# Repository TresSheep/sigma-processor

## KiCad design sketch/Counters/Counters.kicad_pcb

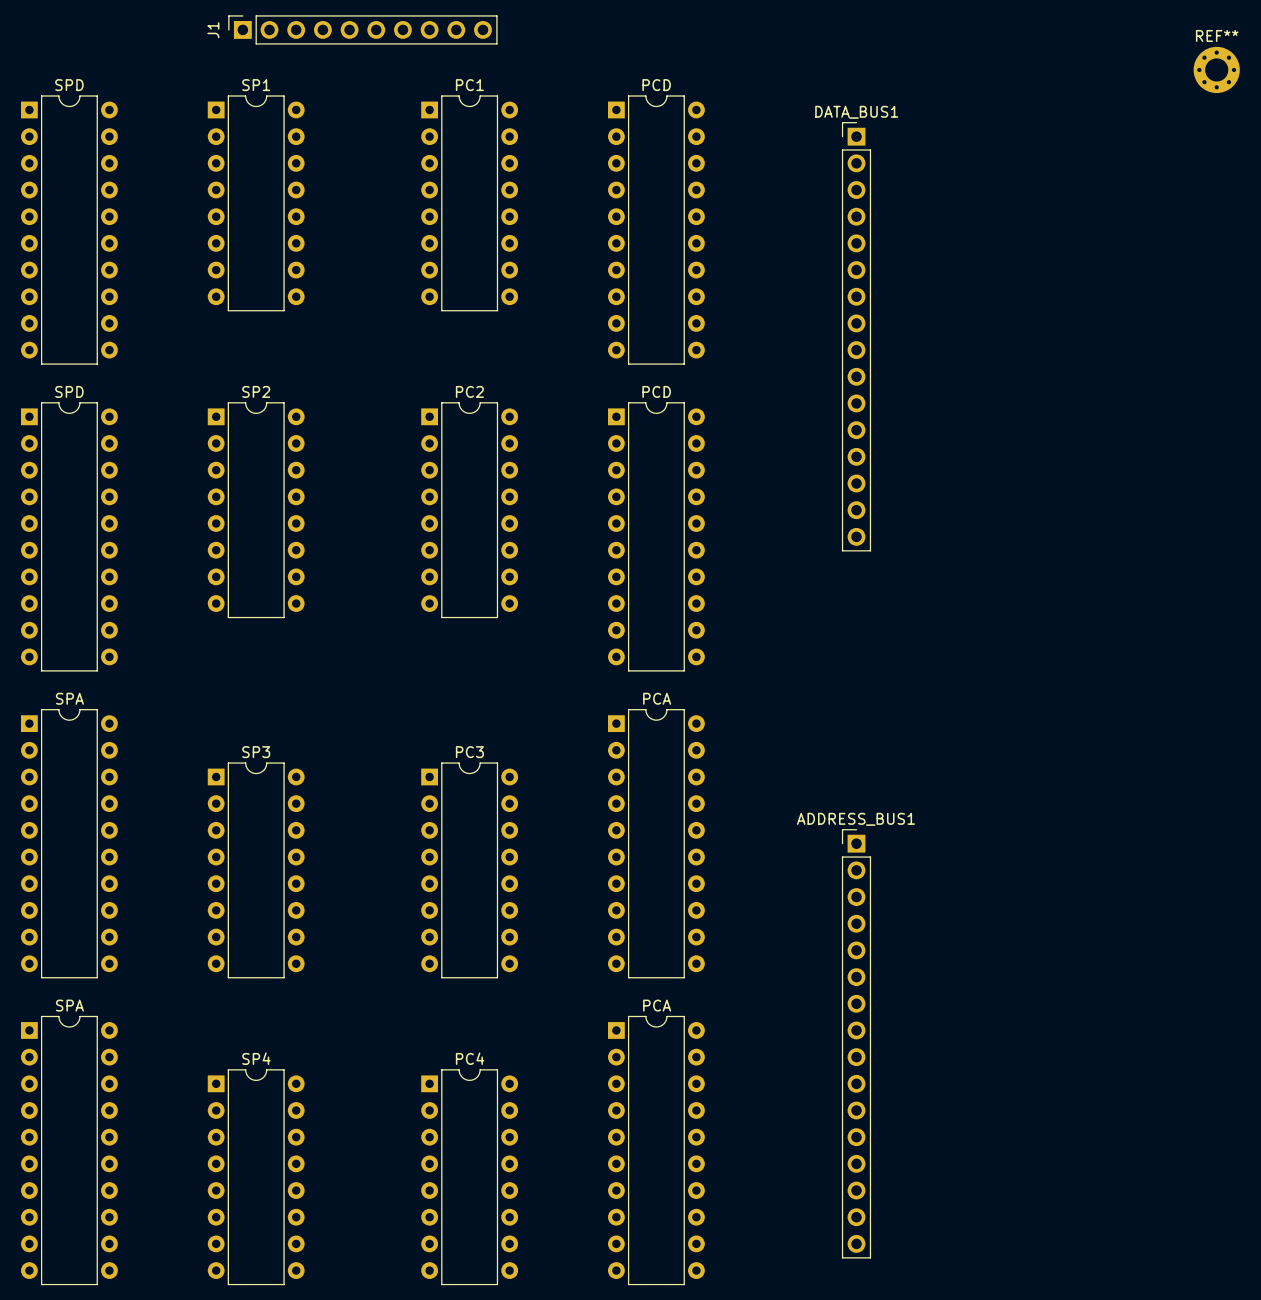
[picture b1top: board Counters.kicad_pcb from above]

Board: 2 copper layers, 19 parts (0 on the bottom side), 80 nets, no tracks yet.

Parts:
ADDRESS_BUS1: Conn_01x16; Socket_Strip_Straight_1x16_Pitch2.54mm
DATA_BUS1: Conn_01x16; Socket_Strip_Straight_1x16_Pitch2.54mm
J1: Conn_01x10; PinSocket_1x10_P2.54mm_Vertical
PC1, PC2, PC3, PC4: SN74F163AN; DIP-16_W7.62mm
PCA: SN74AHCT573N; DIP-20_W7.62mm
PCA#2: SN74AHCT573N; DIP-20_W7.62mm
PCD: SN74AHCT573N; DIP-20_W7.62mm
PCD#2: SN74AHCT573N; DIP-20_W7.62mm
SP1, SP2, SP3, SP4: SN74ALS169BN; DIP-16_W7.62mm
SPA: SN74AHCT573N; DIP-20_W7.62mm
SPA#2: SN74AHCT573N; DIP-20_W7.62mm
SPD: SN74AHCT573N; DIP-20_W7.62mm
SPD#2: SN74AHCT573N; DIP-20_W7.62mm

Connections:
+5V: J1.9, PC1.1, PC1.7, PC1.10, PC1.16, PC2.1, PC2.7, PC2.10, PC2.16, PC3.1, PC3.7, PC3.10, PC3.16, PC4.1, PC4.7, PC4.10, PC4.16, PCA.11, PCA.20, PCA#2.11, PCA#2.20, PCD.11, PCD.20, PCD#2.11, PCD#2.20, SP1.16, SP2.16, SP3.16, SP4.16, SPA.11, SPA.20, SPA#2.11, SPA#2.20, SPD.11, SPD.20, SPD#2.11, SPD#2.20
/DECSP: J1.1, SP1.2
/INCPC: J1.5, PC1.2
/LDPC: J1.6, PC1.9, PC2.9, PC3.9, PC4.9
/LDSP: J1.2, SP1.9, SP2.9, SP3.9, SP4.9
/OEPCA: J1.8, PCA.1, PCA#2.1
/OEPCD: J1.7, PCD.1, PCD#2.1
/OESPA: J1.4, SPA.1, SPA#2.1
/OESPD: J1.3, SPD.1, SPD#2.1
GND: J1.10, PC1.8, PC2.8, PC3.8, PC4.8, PCA.10, PCA#2.10, PCD.10, PCD#2.10, SP1.1, SP1.7, SP1.8, SP1.10, SP2.1, SP2.7, SP2.8, SP2.10, SP3.1, SP3.7, SP3.8, SP3.10, SP4.1, SP4.7, SP4.8, SP4.10, SPA.10, SPA#2.10, SPD.10, SPD#2.10
unnamed: ADDRESS_BUS1.1, PCA.19, SPA.19
unnamed: ADDRESS_BUS1.2, PCA.18, SPA.18
unnamed: ADDRESS_BUS1.3, PCA.17, SPA.17
unnamed: ADDRESS_BUS1.4, PCA.16, SPA.16
unnamed: ADDRESS_BUS1.5, PCA.15, SPA.15
unnamed: ADDRESS_BUS1.6, PCA.14, SPA.14
unnamed: ADDRESS_BUS1.7, PCA.13, SPA.13
unnamed: ADDRESS_BUS1.8, PCA.12, SPA.12
unnamed: ADDRESS_BUS1.9, PCA#2.19, SPA#2.19
unnamed: ADDRESS_BUS1.10, PCA#2.18, SPA#2.18
unnamed: ADDRESS_BUS1.11, PCA#2.17, SPA#2.17
unnamed: ADDRESS_BUS1.12, PCA#2.16, SPA#2.16
unnamed: ADDRESS_BUS1.13, PCA#2.15, SPA#2.15
unnamed: ADDRESS_BUS1.14, PCA#2.14, SPA#2.14
unnamed: ADDRESS_BUS1.15, PCA#2.13, SPA#2.13
unnamed: ADDRESS_BUS1.16, PCA#2.12, SPA#2.12
unnamed: DATA_BUS1.1, PC1.3, PCD.19, SP1.3, SPD.19
unnamed: DATA_BUS1.2, PC1.4, PCD.18, SP1.4, SPD.18
unnamed: DATA_BUS1.3, PC1.5, PCD.17, SP1.5, SPD.17
unnamed: DATA_BUS1.4, PC1.6, PCD.16, SP1.6, SPD.16
unnamed: DATA_BUS1.5, PC3.3, PCD.15, SP3.3, SPD.15
unnamed: DATA_BUS1.6, PC3.4, PCD.14, SP3.4, SPD.14
unnamed: DATA_BUS1.7, PC3.5, PCD.13, SP3.5, SPD.13
unnamed: DATA_BUS1.8, PC3.6, PCD.12, SP3.6, SPD.12
unnamed: DATA_BUS1.9, PC2.3, PCD#2.19, SP2.3, SPD#2.19
unnamed: DATA_BUS1.10, PC2.4, PCD#2.18, SP2.4, SPD#2.18
unnamed: DATA_BUS1.11, PC2.5, PCD#2.17, SP2.5, SPD#2.17
unnamed: DATA_BUS1.12, PC2.6, PCD#2.16, SP2.6, SPD#2.16
unnamed: DATA_BUS1.13, PC4.3, PCD#2.15, SP4.3, SPD#2.15
unnamed: DATA_BUS1.14, PC4.4, PCD#2.14, SP4.4, SPD#2.14
unnamed: DATA_BUS1.15, PC4.5, PCD#2.13, SP4.5, SPD#2.13
unnamed: DATA_BUS1.16, PC4.6, PCD#2.12, SP4.6, SPD#2.12
unnamed: SP1.11, SPA.5, SPD.5
unnamed: SP1.12, SPA.4, SPD.4
unnamed: SP1.13, SPA.3, SPD.3
unnamed: SP1.14, SPA.2, SPD.2
unnamed: SP1.15, SP3.2
unnamed: SP2.2, SP3.15
unnamed: SP2.11, SPA#2.5, SPD#2.5
unnamed: SP2.12, SPA#2.4, SPD#2.4
unnamed: SP2.13, SPA#2.3, SPD#2.3
unnamed: SP2.14, SPA#2.2, SPD#2.2
unnamed: SP2.15, SP4.2
unnamed: SP3.11, SPA.9, SPD.9
unnamed: SP3.12, SPA.8, SPD.8
unnamed: SP3.13, SPA.7, SPD.7
unnamed: SP3.14, SPA.6, SPD.6
unnamed: SP4.11, SPA#2.9, SPD#2.9
unnamed: SP4.12, SPA#2.8, SPD#2.8
unnamed: SP4.13, SPA#2.7, SPD#2.7
unnamed: SP4.14, SPA#2.6, SPD#2.6
unnamed: PC2.2, PC3.15
unnamed: PC2.11, PCA#2.5, PCD#2.5
unnamed: PC2.12, PCA#2.4, PCD#2.4
unnamed: PC2.13, PCA#2.3, PCD#2.3
unnamed: PC2.14, PCA#2.2, PCD#2.2
unnamed: PC2.15, PC4.2
unnamed: PC1.15, PC3.2
unnamed: PC3.11, PCA.9, PCD.9
unnamed: PC3.12, PCA.8, PCD.8
unnamed: PC3.13, PCA.7, PCD.7
unnamed: PC3.14, PCA.6, PCD.6
unnamed: PC4.11, PCA#2.9, PCD#2.9
unnamed: PC4.12, PCA#2.8, PCD#2.8
unnamed: PC4.13, PCA#2.7, PCD#2.7
unnamed: PC4.14, PCA#2.6, PCD#2.6
unnamed: PC1.14, PCA.2, PCD.2
unnamed: PC1.13, PCA.3, PCD.3
unnamed: PC1.12, PCA.4, PCD.4
unnamed: PC1.11, PCA.5, PCD.5

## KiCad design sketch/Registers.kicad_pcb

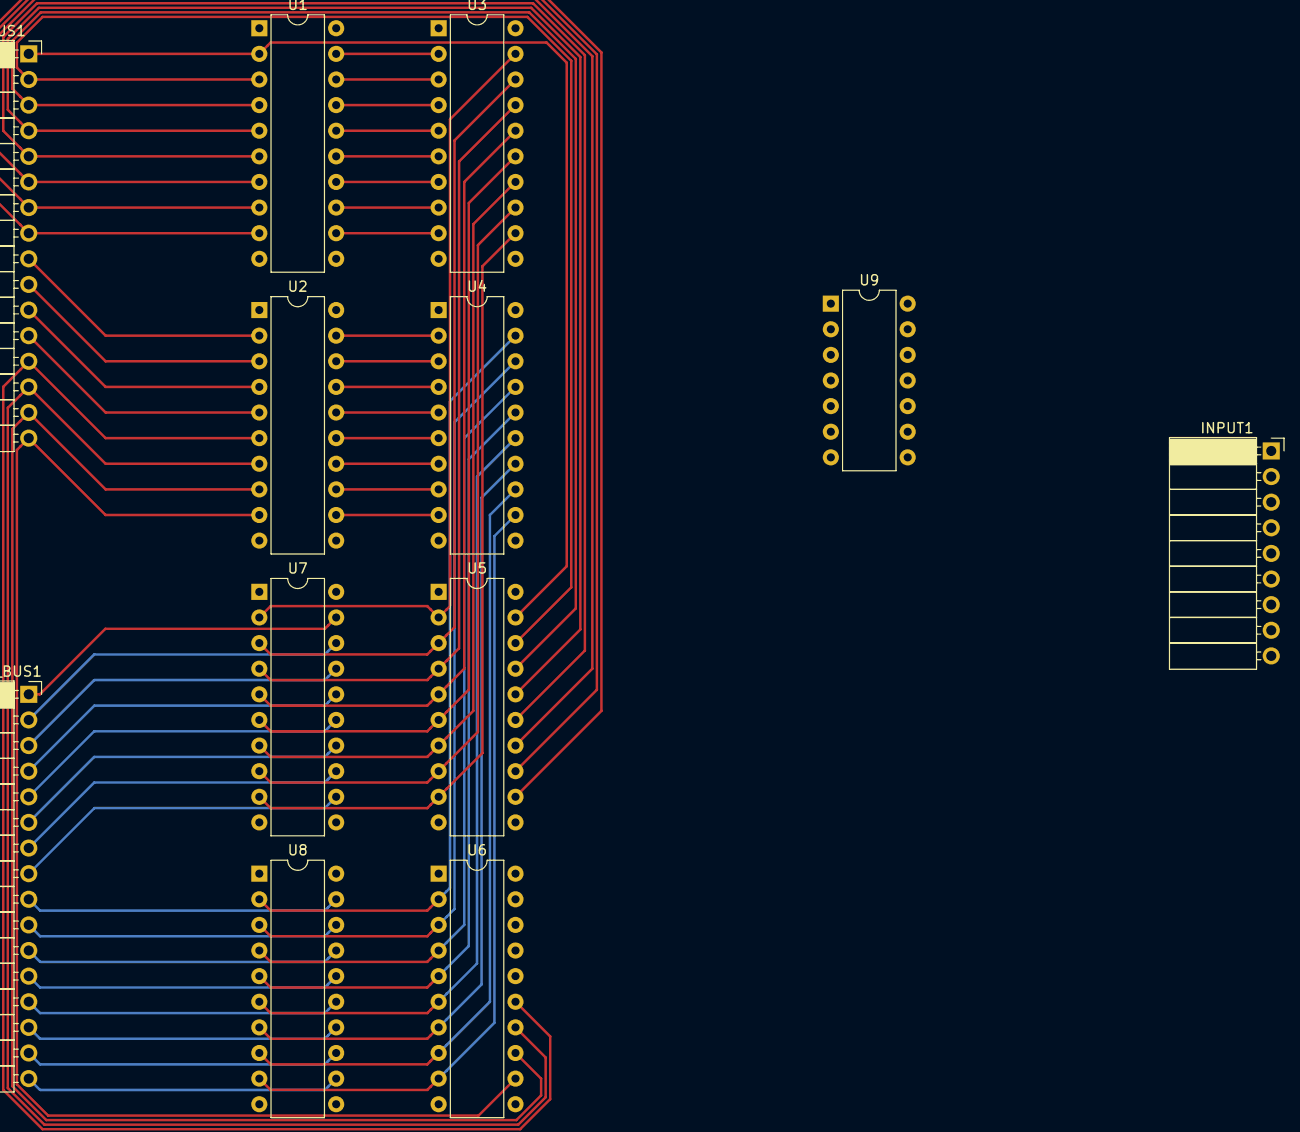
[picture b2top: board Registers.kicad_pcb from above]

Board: 2 copper layers, 12 parts (0 on the bottom side), 77 nets.

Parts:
ADDRESS_BUS1: Conn_01x16; Socket_Strip_Angled_1x16_Pitch2.54mm
DATA_BUS1: Conn_01x16; Socket_Strip_Angled_1x16_Pitch2.54mm
INPUT1: Conn_01x09; Socket_Strip_Angled_1x09_Pitch2.54mm
U1, U2, U5, U6, U7, U8: SN74AHCT573N; DIP-20_W7.62mm
U3, U4: SN74F574N; DIP-20_W7.62mm
U9: SN74AS1004AN; DIP-14_W7.62mm

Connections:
+5V: INPUT1.8, U1.20, U2.20, U3.20, U4.20, U5.11, U5.20, U6.11, U6.20, U7.11, U7.20, U8.11, U8.20, U9.14
/CLK: INPUT1.7, U3.11, U4.11
/LDH: INPUT1.2, U2.11
/LDL: INPUT1.1, U1.11
/OEHA: U8.1, U9.9
/OEHD: U6.1, U9.3
/OELA: U7.1, U9.5
/OELD: U5.1, U9.1
GND: INPUT1.9, U1.1, U1.10, U2.1, U2.10, U3.1, U3.10, U4.1, U4.10, U5.10, U6.10, U7.10, U8.10, U9.7
unnamed: ADDRESS_BUS1.1, U7.19
unnamed: ADDRESS_BUS1.2, U7.18
unnamed: ADDRESS_BUS1.3, U7.17
unnamed: ADDRESS_BUS1.4, U7.16
unnamed: ADDRESS_BUS1.5, U7.15
unnamed: ADDRESS_BUS1.6, U7.14
unnamed: ADDRESS_BUS1.7, U7.13
unnamed: ADDRESS_BUS1.8, U7.12
unnamed: ADDRESS_BUS1.9, U8.19
unnamed: ADDRESS_BUS1.10, U8.18
unnamed: ADDRESS_BUS1.11, U8.17
unnamed: ADDRESS_BUS1.12, U8.16
unnamed: ADDRESS_BUS1.13, U8.15
unnamed: ADDRESS_BUS1.14, U8.14
unnamed: ADDRESS_BUS1.15, U8.13
unnamed: ADDRESS_BUS1.16, U8.12
unnamed: DATA_BUS1.1, U1.2, U5.19
unnamed: DATA_BUS1.2, U1.3, U5.18
unnamed: DATA_BUS1.3, U1.4, U5.17
unnamed: DATA_BUS1.4, U1.5, U5.16
unnamed: DATA_BUS1.5, U1.6, U5.15
unnamed: DATA_BUS1.6, U1.7, U5.14
unnamed: DATA_BUS1.7, U1.8, U5.13
unnamed: DATA_BUS1.8, U1.9, U5.12
unnamed: DATA_BUS1.9, U2.2, U6.19
unnamed: DATA_BUS1.10, U2.3, U6.18
unnamed: DATA_BUS1.11, U2.4, U6.17
unnamed: DATA_BUS1.12, U2.5, U6.16
unnamed: DATA_BUS1.13, U2.6, U6.15
unnamed: DATA_BUS1.14, U2.7, U6.14
unnamed: DATA_BUS1.15, U2.8, U6.13
unnamed: DATA_BUS1.16, U2.9, U6.12
unnamed: INPUT1.3, U9.2
unnamed: INPUT1.4, U9.4
unnamed: INPUT1.5, U9.6
unnamed: INPUT1.6, U9.8
unnamed: U1.12, U3.9
unnamed: U1.13, U3.8
unnamed: U1.14, U3.7
unnamed: U1.15, U3.6
unnamed: U1.16, U3.5
unnamed: U1.17, U3.4
unnamed: U1.18, U3.3
unnamed: U1.19, U3.2
unnamed: U2.12, U4.9
unnamed: U2.13, U4.8
unnamed: U2.14, U4.7
unnamed: U2.15, U4.6
unnamed: U2.16, U4.5
unnamed: U2.17, U4.4
unnamed: U2.18, U4.3
unnamed: U2.19, U4.2
unnamed: U3.12, U5.9, U7.9
unnamed: U3.13, U5.8, U7.8
unnamed: U3.14, U5.7, U7.7
unnamed: U3.15, U5.6, U7.6
unnamed: U3.16, U5.5, U7.5
unnamed: U3.17, U5.4, U7.4
unnamed: U3.18, U5.3, U7.3
unnamed: U3.19, U5.2, U7.2
unnamed: U4.12, U6.9, U8.9
unnamed: U4.13, U6.8, U8.8
unnamed: U4.14, U6.7, U8.7
unnamed: U4.15, U6.6, U8.6
unnamed: U4.16, U6.5, U8.5
unnamed: U4.17, U6.4, U8.4
unnamed: U4.18, U6.3, U8.3
unnamed: U4.19, U6.2, U8.2

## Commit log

2020-01-14 fixed imports
2020-01-15 started pcb
2020-01-15 started on the registers
2020-01-15 counters
2020-01-31 started the program counter
2020-01-31 registers
